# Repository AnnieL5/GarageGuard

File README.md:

# GarageGuard, guard your garage 24/7/365

### What it is

GarageGuard uses a ultrasonic sensor to detect if the garage door is open for a long period of time and makes an alerts until the door is closed.

#### What makes it unique?
It is
- Original
- Simple
- Modifiable
- Made by heart 

### Motivation / Inspiration / Problem

Have you ever had scenarios where you have opened your garage door but it is remained open the next time you checked. 

You realize...oh shoot! The door has been open overnight.

And what's even worse, that there could be animals, like rats, racoons, or even a fox inside your garage.

That's why I designed Garage Guard, your personalized, simple device that alarms you if your garage door is open.

### To use it
To properly use the tool, calibrate the constant to match the distance such that the distance from the product is smaller than the value when door closed and greater otherwise.

After inserting the battery, the device will beep when the door is open for a set period of time.

## Wiring Diagram

## Code example
Go checkout the example code in firmware/GarageGuard and upload it onto the arduino pro mini

For how to upload code onto arduino pro mini using arduino uno, check out https://www.instructables.com/How-to-Program-Arduino-Pro-Mini-Using-Arduino-UNO/

### Image of PCB

### Image of Wiring Schematic

### Image of CAD assembly (without lid)

### Image of CAD assembly (with lid)

## Zine Page

## BOM / Parts Breakdown

| Product name          | Product Description                          | Amount | Unit Price | Shipping Fee | Total Price | Link                                                                                                                                                                                                                                                                                                                                                                                                                                                                                                                                                                                                                                                                            |
|-----------------------|----------------------------------------------|--------|------------|--------------|-------------|---------------------------------------------------------------------------------------------------------------------------------------------------------------------------------------------------------------------------------------------------------------------------------------------------------------------------------------------------------------------------------------------------------------------------------------------------------------------------------------------------------------------------------------------------------------------------------------------------------------------------------------------------------------------------------|
| Ultrasonic sensor     | HC-SR04 3.3-5VNew version                    | 1      | $2.71      |              | $2.71       | https://www.aliexpress.com/item/1005005467178145.html?spm=a2g0o.productlist.main.2.48981450ohptjN&algo_pvid=74ad5a5d-34d5-4956-b985-ef5a75be59a3&algo_exp_id=74ad5a5d-34d5-4956-b985-ef5a75be59a3-1&pdp_ext_f=%7B%22order%22%3A%2210615%22%2C%22spu_best_type%22%3A%22price%22%2C%22eval%22%3A%221%22%2C%22fromPage%22%3A%22search%22%7D&pdp_npi=6%40dis%21CAD%212.71%212.71%21%21%211.94%211.94%21%40210328df17774096350383208e9e52%2112000033197296308%21sea%21CA%216218818596%21X%211%210%21n_tag%3A-29919%3Bd%3A26a99932%3Bm03_new_user%3A-29895&curPageLogUid=PazbM33tgsR5&utparam-url=scene%3Asearch%7Cquery_from%3A%7Cx_object_id%3A1005005467178145%7C_p_origin_prod%3A |
| Passive Buzzer        | 10PCS Passive Buzzer Kits 12085              | 1      | $2.79      |              |  NA         |                                                                                                                                                                                                                                                                                                                                                                                                                                                                                                                                                                                                                                                                                 |
|                       |                                              |        |            |              |             |                                                                                                                                                                                                                                                                                                                                                                                                                                                                                                                                                                                                                                                                                 |
| Arduino Pro Mini      | ÊATMEGA328P 3.3V 8MHz                        | 1      | $6.14      |              | $6.14       | https://www.aliexpress.com/item/1005009384358010.html?spm=a2g0o.detail.0.0.3d69kxh4kxh4TT&mp=1&pdp_npi=6%40dis%21CAD%21CAD+12.34%21CAD+6.19%21%21CAD+6.19%21%21%21%402101e2b217772431183538792e7ffd%2112000048937356319%21ct%21CA%216218818596%21%211%210%21                                                                                                                                                                                                                                                                                                                                                                                                                    |
| AA Battery            |                                              | 1      |  NA        |              |             |                                                                                                                                                                                                                                                                                                                                                                                                                                                                                                                                                                                                                                                                                 |
| THT Battery Holder    | 14500 Battery Box With Pins 1AA 1.5V         | 1      | $0.33      | $7.48        | $0.33       | https://www.aliexpress.com/item/1005005620966310.html?spm=a2g0o.cart.0.0.358a38dadNcuNR&mp=1&pdp_npi=6%40dis%21CAD%21CAD+0.38%21CAD+0.32%21%21CAD+0.32%21%21%21%402101eee917774109006605329ec0dc%2112000033776650718%21ct%21CA%216218818596%21%215%210%21                                                                                                                                                                                                                                                                                                                                                                                                                       |
| Voltage Regulator     | 0.8V-5V to 3V 3.3V 5V Boost Voltage Regulate | 1      | $3.85      |              | $3.85       | https://www.aliexpress.com/item/1005006167931077.html?spm=a2g0o.detail.0.0.4a7cjdtRjdtRpQ&mp=1&pdp_npi=6%40dis%21CAD%21CAD+3.96%21CAD+3.86%21%21CAD+3.86%21%21%21%402101d6ff17773444964128610e94da%2112000036084126229%21ct%21CA%216218818596%21%211%210%21                                                                                                                                                                                                                                                                                                                                                                                                                     |
|                       |                                              |        |            |              |             |                                                                                                                                                                                                                                                                                                                                                                                                                                                                                                                                                                                                                                                                                 |
| m3 self-tapping screw | ZONSANTA M3x50pc 5mm                         | 1      | $2.79      |              | $2.79       | https://www.aliexpress.com/item/4000982209705.html?spm=a2g0o.productlist.main.2.5e0a5049GO2c6k&algo_pvid=d9d1041d-5b82-4d1d-adb8-2c50ae22e721&algo_exp_id=d9d1041d-5b82-4d1d-adb8-2c50ae22e721-1&pdp_ext_f=%7B%22order%22%3A%2214058%22%2C%22eval%22%3A%221%22%2C%22fromPage%22%3A%22search%22%7D&pdp_npi=6%40dis%21CAD%212.04%211.99%21%21%211.46%211.42%21%40210328d417774091351247794e1c13%2110000013191635027%21sea%21CA%216218818596%21X%211%210%21n_tag%3A-29919%3Bd%3A26a99932%3Bm03_new_user%3A-29895&curPageLogUid=Y5TAugc4ns7L&utparam-url=scene%3Asearch%7Cquery_from%3A%7Cx_object_id%3A4000982209705%7C_p_origin_prod%3A                                           |
| head pins             | 5 male 5 female                              | 1      | $5.19      |              | $5.19       | https://www.aliexpress.com/item/1005007235591794.html?spm=a2g0o.cart.0.0.31e138dackOqlz&mp=1&sourceType=570&pdp_npi=6%40dis%21CAD%21CAD+16.72%21CAD+5.19%21%21CAD+5.19%21%21%21%402103119c17773470443845760e9623%2112000039908542823%21ct%21CA%216218818596%21%211%210%21&pdp_ext_f=%7B%22cart2PdpParams%22%3A%7B%22sourceType%22%3A%22570%22%2C%22cartSource%22%3A%22main%22%7D%7D                                                                                                                                                                                                                                                                                             |
|                       |                                              |        |            |              |             |                                                                                                                                                                                                                                                                                                                                                                                                                                                                                                                                                                                                                                                                                 |
| Total                 |                                              |        |            |              | $23.30      |                                                                                                                                                                                                                                                                                                                                                                                                                                                                                                                                                                                                                                                                                 |

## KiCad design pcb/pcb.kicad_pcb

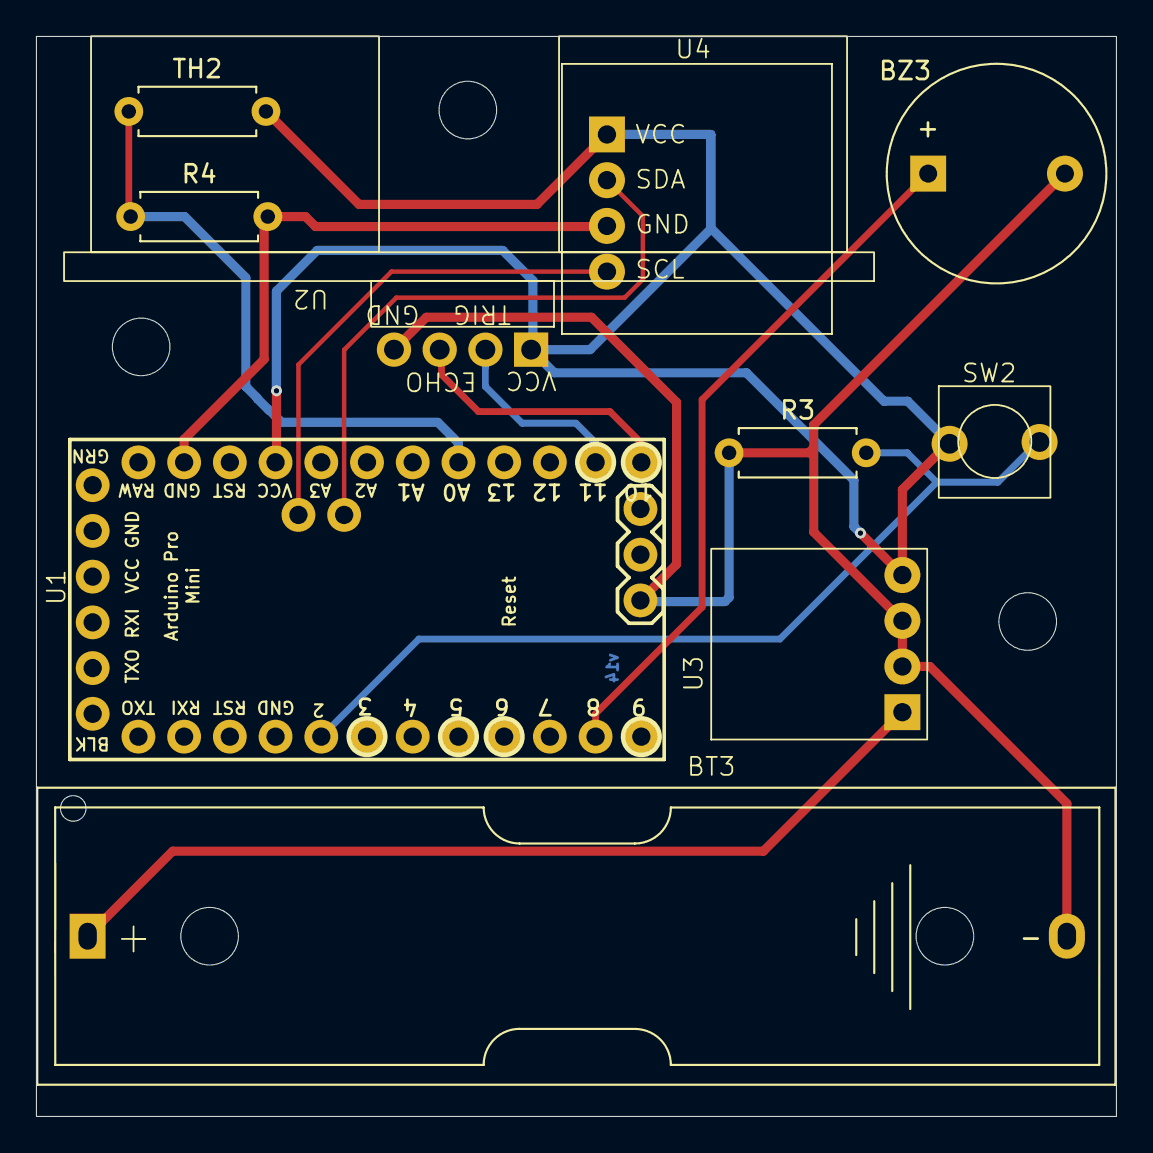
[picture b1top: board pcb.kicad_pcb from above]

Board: 2 copper layers, 60.0 x 60.0 mm, 10 parts (0 on the bottom side), 11 nets.

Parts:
BT3: Battery_Cell; 6s-aa 14500
BZ3: Buzzer; Buzzer_12x9.5RM7.6
R3: 4.7k; R_Axial_DIN0207_L6.3mm_D2.5mm_P7.62mm_Horizontal
R4: 100k; R_Axial_DIN0207_L6.3mm_D2.5mm_P7.62mm_Horizontal
SW2: SW_Push; Button_2pin
TH2: Thermistor; R_Axial_DIN0207_L6.3mm_D2.5mm_P7.62mm_Horizontal
U1: arduino_pro_mini_new
U2: Ultrasonic Sensor HC-SR04
U3: ND0205MA Voltage Regulator
U4: AHT20+BMP280

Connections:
+1.5V: BT3.1 (+), U3.1 (Vi)
+3.3V: SW2.1, TH2.2, U1.r4 (VCC), U2.1 (VCC), U3.4 (Vo), U4.1 (VIN)
GND: BT3.2 (-), BZ3.2 (-), R3.1, U1.b1 (GND), U2.4 (GND), U3.2 (GND), U3.3 (GND)
unnamed: BZ3.1 (+), U1.l2 (8)
unnamed: R3.2, SW2.2, U1.l8 (2)
unnamed: U1.r12 (10), U2.3 (ECHO)
unnamed: U1.r11 (11), U2.2 (TRIG)
unnamed: R4.1, TH2.1, U1.r8 (A0)
unnamed: U1.m1 (A4), U4.2 (SDA)
unnamed: U1.m2 (A5), U4.4 (SCL)
unnamed: R4.2, U1.r2 (GND), U4.3 (GND)

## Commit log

2026-04-20 4.19
2026-05-11 5.10
2026-05-16 5.16
2026-05-16 update readme - images
2026-06-16 6.16
2026-06-16 update BOM on readme
2026-06-20 6.20
2026-06-20 add zine page onto readme
